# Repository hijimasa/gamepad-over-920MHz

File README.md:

# gamepad-over-920MHz

**USB ゲームパッドを 920MHz 帯（IM920sL）で無線化する**ファームウェアです。
Bluetooth より遠くまで届く無線リンクに載せ替えつつ、PC からは**普通のゲームパッドのまま**に見せます。
ロボットの遠隔操縦を想定しています。

```
[USBゲームパッド] ─USB(PIO-USB)→ [送信機 XIAO RP2040] ─UART→ [IM920sL]
                                                                 │ 920MHz
[PC] ←USB HID + CDC─ [受信機 XIAO RP2040] ←UART─ [IM920sL] ←─────┘
```

## 特徴

- **軸番号・ボタン番号が元のパッドと一致する。** 送信機がパッドの HID レポート
  ディスクリプタを解析して軸構成を無線で送り、受信機がそれに合わせて HID
  ディスクリプタを実行時に組み立てます。**受信機側の設定は不要**で、
  `/dev/input/js0` の番号が直挿しと同じになるので、既存のソフトをそのまま使えます。
- **フェイルセーフ。** 有効なパケットが 300ms 途絶えると、受信機は全軸中立・
  全ボタン OFF を出力します（実測で約 300ms、ログにも残ります）。
- **リンクの生死が送信機側でも分かる。** 受信機から 2 秒ごとにハートビートを返し、
  「受信機が前方向を受信できているか」まで含めて LED に反映します。
- **チャンネル自動選定。** 起動時に 31〜45 の雑音を測って空いているチャンネルへ移動します。
  複数ペアを同時に運用しても電波を取り合いません。通信が途絶えたら待ち合わせ用の
  ch31 へ自動で戻ります。
- **暗号化（AES-GCM 256bit）。** 同じグループ番号さえ合えば誰でも操作できてしまう
  状態を防げます。
- **USB CDC コンソール。** 設定・ペアリング・電波品質の確認・配線の切り分けができます。

Linux と Windows の両方で動作を確認しています（macOS は未確認ですが、標準の HID と
CDC しか使っていないため動く見込みです）。

## 必要なもの

| | 品目 | 備考 |
|---|---|---|
| 送信機 | Seeed XIAO RP2040 ×1 | CPU 240MHz で動かす（PIO-USB の要件） |
| 送信機 | IM920sL ＋ IM920sL-ADP ×1 | 変換アダプタ経由で 2.54mm に |
| 送信機 | USB Type-A メスコネクタ | ゲームパッド接続用 |
| 送信機 | モバイルバッテリー | 実測の消費電流は約 60mA |
| 受信機 | Seeed XIAO RP2040 ×1 | PC に USB-C で接続 |
| 受信機 | IM920sL ＋ IM920sL-ADP ×1 | |

配線は [docs/schematic/gamepad_wireless_schematic.svg](docs/schematic/gamepad_wireless_schematic.svg)（Rev.3）、
部品表は [docs/gamepad_wireless_BOM.xlsx](docs/gamepad_wireless_BOM.xlsx) を参照してください。

基板（送信機・受信機で共通、100×62mm 2層）の KiCad データと発注用ガーバーは
[hardware/](hardware/) にあります。ブレッドボードやユニバーサル基板で組む場合は
[docs/netlist.md](docs/netlist.md) にネットリストとレイアウト制約があります。

> IM920sL 本体と変換アダプタの取扱説明書は、メーカー（インタープラン）の配布物なので
> リポジトリには含めていません。<https://www.interplan.co.jp/> から入手し、
> `docs/IM920sL_manual.pdf` / `docs/IM920sL_ADP_manual.pdf` として置くと、
> 本 README 中の参照（コマンド仕様・端子表・チャンネル表）と対応します。

## 最短の始め方

```bash
# 1. ビルド環境（arduino-cli）
arduino-cli config add board_manager.additional_urls \
  https://github.com/earlephilhower/arduino-pico/releases/download/global/package_rp2040_index.json
arduino-cli core update-index
arduino-cli core install rp2040:rp2040
arduino-cli lib install "Pico PIO USB" "Adafruit NeoPixel"

# 2. 書込み
./build.sh rx upload /dev/ttyACM0   # 受信機
./build.sh tx upload /dev/ttyACM1   # 送信機

# 3. ペアリング（初回だけ。両機を 50cm 以内に置く）
#    起動後 5 秒以内（LED が水色の速い点滅）か、赤点滅中に
#    受信機 → 送信機 の順に BOOTSEL を 3 秒以上長押し

# 4. 確認
tools/jsinfo.py 10     # /dev/input/js0 の軸数・ボタン数とライブの値
```

うまくいくと**両機とも緑点灯**になり、PC に `irlab Wireless Gamepad` として
ゲームパッドが現れます。

詳しい操作は[操作（BOOTSEL ボタン ／ CDC コンソール）](#操作bootsel-ボタン--cdc-コンソール)、
うまくいかないときは[診断に使えるコマンド](#診断に使えるコマンド)を参照してください。

## 免責

**個人が趣味・研究用に作った原理試作です。**動作・性能・安全性のいずれも保証しません。

- 無線の到達距離や通信の安定性は、設置場所の電波環境に大きく左右されます。
  同じ構成でも結果は異なります。
- ロボットなど**物理的に動くものを制御する用途では、本装置とは独立した非常停止手段を
  必ず用意してください。**受信側に 300ms のフェイルセーフを実装してありますが、
  これは「通信が途絶えたら中立を出力する」だけのもので、機器の安全を保証するものでは
  ありません。
- 本リポジトリの成果物（ファームウェア、回路図、基板データ、資料）を使用した結果
  生じたいかなる損害についても、作者は責任を負いません。
- 920MHz 帯の利用は国と地域の法令に従ってください。IM920sL は日本国内の電波法認証を
  取得済みの製品ですが、**モジュールを改造したり国外で使用したりする場合は、
  使用者の責任において適法性を確認してください。**

不具合や改善点を見つけたら Issue や Pull Request で教えていただけると助かります。

## ライセンス

MIT License（[LICENSE](LICENSE)）。無保証です（上記「免責」および LICENSE の
"AS IS" 条項を参照）。

---

以下は実装と実機検証の詳細です。立ち上げで踏んだ問題（PIO-USB の 240MHz 要件、
TxD/RxD 逆接続の切り分け、コア1 だけが死ぬ故障モードなど）も記録してあります。

## ビルドと書込み

```bash
./build.sh tx                       # 送信機をビルド
./build.sh rx                       # 受信機をビルド
./build.sh tx upload /dev/ttyACM0   # ビルドして書込み
```

必要な環境:

- arduino-cli ＋ `rp2040:rp2040`（earlephilhower コア）
- ライブラリ `Pico PIO USB`、`Adafruit NeoPixel`
- FQBN
  - TX: `rp2040:rp2040:seeed_xiao_rp2040:usbstack=tinyusb,freq=240`
    （PIO-USB は 12MHz の倍数が必要。**120MHz ではタイミング余裕が足りず列挙に失敗した**ので 240MHz。
    `WG_FREQ=120 ./build.sh tx` で変更可）
  - RX: `rp2040:rp2040:seeed_xiao_rp2040:usbstack=tinyusb`

書込みは 1200bps タッチで自動的にブートローダへ入る。入らないときは BOOTSEL を押しながら
USB を挿し、`RPI-RP2` に `build/<role>/*.uf2` をコピーする。

## 構成

```
firmware/common/     TX・RX 共通（arduino-cli には --library で渡す）
  packet.h           無線パケット（State 12 バイト / Info 10 バイト）
  im920sl_config.h   IM920sL の設定・送受信（元からあったもの＋追記）
  im920_diag.h       配線切り分け用の diag / raw / scan
  hid_gamepad_map.h  パッドの HID ディスクリプタを解析して状態を取り出す（TX）
  hid_desc_builder.h HID ディスクリプタを実行時に組み立てる（RX）
  status_led.h       オンボード LED の状態表示
firmware/tx/tx.ino   送信機
firmware/rx/rx.ino   受信機
tools/console.py     CDC コンソールにコマンドを送る補助ツール
```

## 状態表示 LED

XIAO RP2040 のオンボード NeoPixel（GPIO12／電源 GPIO11）と三色 LED（R17/G16/B25）を同時に駆動する。

| 色 | 状態 |
|---|---|
| 赤の点滅 | 接続なし（TX: パッド未接続か送信が通らない／RX: フェイルセーフ中） |
| 黄の点滅 | ペアリング中 |
| 緑の点灯 | 接続中（送信機は**受信機からの応答が届いている**ときだけ） |
| 青の点灯 | 設定ブリッジ中 |
| 白の点滅 | 起動処理中 |
| **水色の速い点滅** | **BOOTSEL ボタン受付中（起動直後 5 秒）** |
| 赤紫の速い点滅 | IM920sL の設定に失敗 |

## 操作（BOOTSEL ボタン ／ CDC コンソール）

SW1 は未実装なので **BOOTSEL ボタン**を使う。電源投入時に押したままだと書込みモードに
入ってしまうため、**電源を入れてから押す**必要がある。押せるタイミングは 2 つ:

**1. 起動直後の受付ウィンドウ（LED が水色の速い点滅、5 秒間）**

電源を入れると 白点滅（起動処理）→ **水色の速い点滅（受付中）** と変わる。
水色の間に押す。

**2. 運用中、リンクが確立していないとき（LED が赤点滅）**

組み立て直後でまだペアリングしていない状態は赤点滅になるので、**そのまま押せばよい**。
緑点灯（正常動作中）のときはボタンを一切読まないので、運用中の通信を乱すことはない。

- 短押し（3 秒未満）→ 設定ブリッジ
- **3 秒以上の長押し → ペアリング**（TX＝子機、RX＝親機。両機を 50cm 以内に置く）

押している間は LED が黄点滅になるので、3 秒の長押しはそれを見ながら数えられる。

> BOOTSEL の読み取りは XIP（フラッシュ実行）を一瞬止めてもう一方のコアを idle にするため、
> PIO-USB が動作中は避けたい。そのため送信機では、パッドが列挙済みになるか起動から
> 15 秒経つまでは運用中のポーリングを行わない。

### 組み立て後の初回手順

1. 受信機を PC に、送信機にゲームパッドとモバイルバッテリーを繋ぐ
2. 両方とも赤点滅になる（＝まだペアリングしていない）
3. 両機を 50cm 以内に置く
4. **受信機の BOOTSEL を 3 秒以上長押し**（親機として登録パケットを送る）
5. すぐに**送信機の BOOTSEL も 3 秒以上長押し**（子機として受け取る）
6. 成功すると両方とも緑点灯になる

ペアリングは Flash に保存されるので**初回だけ**でよい（[ペアリングは初回だけ](#ペアリングは初回だけ) 参照）。

USB-C の CDC コンソール（`tools/console.py` か `screen /dev/ttyACM0 115200`）:

| コマンド | 内容 |
|---|---|
| `help` | コマンド一覧 |
| `status` | IM920sL の設定値、受信状況（RSSI・seq 欠番）、パッドの状態 |
| `config` | AutoConfig（目標値と違う項目だけ ENWR で書込み） |
| `pair` | ペアリング |
| `bridge` | USB CDC ↔ IM920sL の透過ブリッジ |
| `dump` | （TX）HID 生レポートの表示 |
| `map` | （TX）解析した HID マップ |
| `profile` / `reset` | （RX）HID 構成の表示／既定値に戻して再起動 |
| `diag` / `raw <cmd>` / `scan` | IM920sL の配線・応答の切り分け |

## ペアリングは初回だけ

グループ番号は `ENWR` でモジュールの Flash に書かれる不揮発設定なので、電源を切っても残る。
実測（両機を再起動して確認）:

```
再起動前: TX RDGN=0001D9D8 / RX RDGN=0001D9D8
再起動後: TX RDGN=0001D9D8 / RX RDGN=0001D9D8   ← 保持
link: UP  RSSI=-19dBm  packets=116 bad=0        ← 自動で復帰
```

ペアリングが要るのは **初回**と、**どちらかのモジュールを交換したとき**
（グループ番号は親機の固有 ID から決まる）、あるいは `RDGN` が `FFFFFFFF` に
戻ってしまったときだけ。**ファームを書き直しても不要**（`im920AutoConfig()` は
STNN/STRT/STCH/STPO/STTR しか触らない）。

⚠ Flash の書換えは全項目合計で 10 万回まで。ペアリングを不必要に繰り返さないこと。
`im920AutoConfig()` も「目標値と違う項目だけ」書くので、設定が合っていれば書き込まない。

## 軸番号・ボタン番号を元のパッドに合わせる仕組み

既存の操縦ソフトが `/dev/input/js0` を直接読んでいる場合、軸とボタンの並びが
元のパッドと一致していないと、受信機に差し替えた途端に割り当てがずれる。
joydev は **ABS\_\* コードの昇順**に軸番号を振る
（X=0, Y=1, Z=2, Rx=3, Ry=4, Rz=5, Hat=6,7）ので、**元のパッドに在る軸の集合**が
一致していれば番号も一致する。そのため、

1. TX は VID:PID の決め打ち表ではなく、**HID レポートディスクリプタを解析**して
   Usage（X, Y, Z, Rx, Ry, Rz, Hat switch, Button 1..n）の位置を求める。
   → どのパッドでも Linux の hid-generic と同じ割り当てになる。
2. TX は軸の種類（axisMask）とボタン数を **Info パケット**で 2 秒ごとに送る。
3. RX は受け取った構成を EEPROM に保存し、**HID ディスクリプタを実行時に組み立てる**。
   構成が変わったときは保存して自動で再起動し、新しいディスクリプタで列挙し直す。

つまり **受信機側の設定は不要**。送信機にパッドを繋げば、受信機が自動的に同じ形の
ゲームパッドとして PC に見えるようになる（初回は 1 回だけ自動再起動する）。

`dump` で生レポート、`map` で解析結果、RX の `profile` で現在の構成を確認できる。

## Linux 以外の OS で使えるか

受信機は標準的な **USB HID ゲームパッド＋CDC の複合デバイス**なので、Windows / macOS でも
追加ドライバなしで動く。実際のディスクリプタ:

```
bDeviceClass 239 / bDeviceSubClass 2 / bDeviceProtocol 1   ← IAD 複合デバイス宣言
  インタフェース 0,1: CDC（Communications + CDC Data）
  インタフェース 2  : HID（Usage Page = Generic Desktop, Usage = Game Pad）
```

- **HID**: Windows 標準の HID ドライバで動く。`joy.cpl`・DirectInput・RawInput から見える。macOS も標準対応
- **CDC**: Windows 10/11 は `usbser.inf` 内蔵で COM ポートとして見える。macOS は `/dev/cu.usbmodem*`
- **IAD 宣言**がないと Windows が複合デバイスを正しく分解できないが、TinyUSB が付けている

### 注意点

- **XInput ではない**。Windows で XInput 専用のゲームからは見えない。
  これは F310 を D モードで使うのと同じ制約。
  DirectInput / RawInput 対応のソフトなら問題ない。
- 軸・ボタン番号は、Linux の joydev が ABS コード順、Windows の DirectInput が
  HID Usage 順で決まるので、同じ Usage を出している限り一致するはず。**Windows 実機は未確認**。
- VID:PID は Adafruit の既定値 `239a:cafe` のまま。機能上は問題ないが、
  外部に配布するなら自前の PID を用意するのが望ましい。

### Windows 向けに入れてある対策

1. **シリアル番号の衝突回避** — 手元の 2 枚は同じチップ ID（`4250305539333104`）を返す。
   Windows は VID/PID/シリアルでインスタンスを識別するため、同じ PC に両方挿すと衝突しうる。
   役割の接頭辞を付けている（`WGTX-...` / `WGRX-...`）。
2. **HID ディスクリプタのキャッシュ対策** — Windows はレポートディスクリプタを
   VID/PID/**REV** 単位でキャッシュする。受信機はプロファイル学習でディスクリプタを
   作り直すので、構成から `bcdDevice` を生成して別リビジョンとして見せている
   （例: axisMask 0x27・ボタン 12・ハットあり → `bcdDevice = 27.19`）。

## 取扱説明書との照合（docs/IM920sL_manual.pdf Rev.1.5）

公式資料と全コマンド・全設定値を突き合わせ済み。**仕様違反は無かった。**

- **ch31＋高速モード（STRT 1）は仕様上有効**。`STCH` は「01〜29、31〜45」とだけ規定され、
  通信モードによる制限は無い（モードが決めるのは既定値のみ）。
  4s モード（31〜45）は「1 時間あたりの送信時間の総和 **制限なし**」と明記。
  電波法上の処理はモジュール内部で自動なので、ファーム側で duty を管理する義務は無い。
- 発行している 14 コマンドの名称・引数書式・応答・前提条件・順序依存はすべて資料どおり
  （`STNN 0001` に ENWR 必須、`STRT`→`STCH` の順、ペアリング後は RESET 端子必須）。
- 受信行 `aa,bbbb,dd:`、**RSSI は符号付き**（`9Ch`=−100dBm）、TXDA は 1〜32 バイト、
  送信時間 `4.56ms + 80µs × バイト数`（12 バイトで 5.52ms）— すべて一致。
- 触っている設定は次の 5 つだけ（それ以外は初期値のまま）。

  | コマンド | 内容 | 設定値 |
  |---|---|---|
  | `STNN` | ノード番号 | 受信機（親機）= **0001**、送信機 = **0002** |
  | `STRT` | 通信モード | **1**（高速 100kbps） |
  | `STCH` | チャネル | **31**（起動後に空きチャネルへ移動） |
  | `STPO` | 送信出力 | **2**（10mW） |
  | `STTR` | キャリアセンス NG 時の自動リトライ | **00**（再送はファーム側で判断する） |

- **ADP の J1/J2 対応**も回路図で確認。`J1-n = 本体 pin(2n−1)`、`J2-n = pin(2n)`。
  本体 pin1 は資料により `IO1/BUSY`、ADP 回路図では `IO1/RTS` と表記が違うが同じ端子。

### ユニキャストと ACK について

`TXDU`（ユニキャスト）は実在し「**OK は相手に届いたことを示す**」と明記されている。
ただし**ルート探索を行い、失敗時は自動で最大 10 回リトライ**するため遅延が大きくばらつく
（資料も「リアルタイム性が要求される用途では十分ご注意ください」と注意喚起）。
30ms 周期の操縦データには不向きなので採用していない。

各パケットは差分ではなく**現在の全状態**を持つので、落ちても次のパケットが完全に
上書きする。再送は「古い状態を届けたうえに新しい状態を遅らせる」ため逆効果。
取りこぼしへの対処は受信側の 300ms フェイルセーフで行う。

なお `TXSB`（センドバック送信）はルート探索なしで送信元へ返せるので、
ハートビートをブロードキャストからユニキャストに変えたい場合の選択肢になる（未採用）。

### 4s モードの送信休止規定（2026-09-19 に再確認）

取扱説明書 表1・§7-3 より、ch31〜45（4s モード）の規定は次のとおり。

| 項目 | 4s モード（ch31〜45） | 360s モード（ch01〜29） |
|---|---|---|
| キャリアセンス時間 | 約 6ms | 128µs〜1ms |
| 送信休止時間 | **52ms 以上** | 2ms 以上 |
| 1 時間あたりの送信時間の総和 | **なし** | 360 秒以内 |
| 送信時間制限 | 3.9 秒以下 | 400ms 以下 |

「1 時間 360 秒」の総和制限は ch01〜29 だけの話で、本プロジェクトの ch31〜45 には無い。

代わりに効くのが**送信休止 52ms** で、挙動は「最初の送信から 3.9 秒を超えたら 52ms 休止」
「4 秒経過前に 52ms 以上空けば窓がリセットされる」。
1 回の占有はキャリアセンス約 6ms ＋ 送信 6ms（12 バイト時 5.52ms を切り上げ）＝ 約 12ms
なので、計算上は **64ms 間隔**あれば窓がリセットされ続けるはず。

**ただし実測はこの計算と合わない。** ブリッジ経由でファームを介さず TXDA を打った結果:

| 送信間隔 | 55ms | 65ms | 75ms | 90ms | 120ms | 150ms |
|---|---|---|---|---|---|---|
| NG 率 | 20.0% | 17.5% | 12.5% | 8.0% | 4.0% | **0%** |

64ms を超えても NG は残り、0 になるのは 150ms 以上。**機構は特定できていない。**

なお **NG は一度も連続しなかった**（90ms で 12 回、120ms で 6 回、すべて単発）。
欠落は最悪 2 周期分なので、受信側フェイルセーフ 300ms には届かない。

⚠ 暗号化を有効にすると 1 パケットが **24 バイト増える**（§7-4）ので、
12 バイトのパケットは 36 バイト相当（7.44ms）になる。上の測定は暗号化なしの値。

## UART の高速化（115200bps）

12 バイト送信の UART 時間は 19200bps で約 16ms あり、**電波の送信時間 5.5ms の 3 倍**を
食っていた。`SBRT 7` で 115200bps にすると約 2.7ms になる。

`SBRT` は資料に「Flash メモリに記憶します」の記載が無く揮発性とみられるため、
**毎起動で設定しても Flash 書換え回数を消費しない**。起動時に `im920SetupBaud()` が
`RDVR` の応答でモジュールの現在のボーレートを判別し、必要なら 115200 に上げる。
判別に失敗したときは元のボーレートのまま動作を続ける。

## パケット暗号化＋送信元認証

AES-GCM 256bit。**同じグループ番号さえ合えば誰でもロボットを操作できる**状態を防ぐ。

```
enc <16進64桁>   キーを設定して有効化（両機に同じキーを入れること）
enc off          無効化（キーは残る）
```

- `STKY` は ENWR 中のみ実行可能で Flash に記憶される（読出しコマンドは無い）ため、
  明示的なコマンドのときだけ設定する
- 通信時間が 24 バイト分（高速モードで約 1.9ms）増える
- ペアリング（STGN）時は常に非暗号化パケットなので、順序はどちらでもよい
- 実測: 暗号化オンで `ng=0%`、`bad=0`、`lostEvents=0`

## 無線パケット

**State（12 バイト。30〜100ms ごと）**

| オフセット | 内容 |
|---|---|
| 0 | seq |
| 1–2 | buttons（u16 LE、bit0 = ボタン 1） |
| 3 | hat（0〜7 が方向（0=上、時計回り）、8 = 中立） |
| 4–9 | 軸 6 個 = **X, Y, Z, Rx, Ry, Rz**（0x80 が中立。スティック/トリガではなく **HID Usage 順**で並べている。理由は「軸番号・ボタン番号を元のパッドに合わせる仕組み」を参照） |
| 10 | flags（bit0: パッド接続中） |
| 11 | checksum（byte0〜10 の XOR） |

**Heartbeat（4 バイト。受信機 → 送信機、2 秒ごと）**
`0xC3`, seq, 受信機側の RSSI(i8), XOR。

`TXDA` はブロードキャストで ACK がないため、送信機は自分の電波が届いたかを知る手段がない。
そのままだと送信機の緑は「モジュールが送信を受理した」ことしか意味せず、
**受信機の電源が落ちていても緑**になってしまう。そこで受信機から定期的に投げ返し、
送信機はこれが 1.5 秒途切れたら赤点滅にする。受信機側の RSSI も載せているので、
送信機のコンソールで**両方向の電波強度**が見える（距離試験に便利）。

⚠ **周期を短くすると前方向のパケットが落ちる。** 半二重なので、受信機が
ハートビートを送っている間はパッドのパケットを受け取れない。実測:

| ハートビート周期 | 受信パケット | seqDrop | 300ms 途絶の回数 |
|---|---|---|---|
| 500ms | 11502 | 901（7.8%） | 870 |
| 2000ms | 203 | 0（0%） | 0 |

送信機の NG 率（キャリアセンス）は 2Hz でも +1% 程度しか増えないので、
一見すると安く見えるが、**効いてくるのは受信側の取りこぼし**のほう。
既定は 2 秒、送信機のリンク判定タイムアウトは 5 秒。
受信機は応答を待たずに投げる（`im920SendNoWait`）ので HID の処理は止まらない。

**Info（10 バイト。2 秒ごと）** `0xA5`, version, axisMask, buttonCount, caps(bit0=hat), VID, PID, XOR。
長さでどちらのパケットか判別する。

送信は「状態が変わったら即送信＋無変化でも 100ms ごと」「最短間隔 30ms」。`TXDA` が NG でも
再送はせず次の周期に任せる。

## 動作中に突然リンク断になる問題（2026-09-19 修正）

送信機のモジュールは**半二重**で、自分が送信している間は受信できない。
そのため送信間隔によって、受信機からのハートビートの取りこぼし率が大きく変わる。

| 送信間隔 | ハートビート欠落 |
|---|---|
| 60ms（パッド静止） | 6.6% |
| **30ms（操作中）** | **29.5%** |

ハートビートは 2 秒周期なので、旧設定の `HB_TIMEOUT_MS = 5000` では
**2 回連続で落ちるだけ**（操作中は 8.7%／2 秒ごと）でリンク断と誤判定していた。
平均 20〜30 秒に 1 回、動作中に突然赤点滅する原因。

さらに `CH_REVERT_MS = 12000` も同じハートビート頼りで、6 回連続の欠落で
ch31 に戻って再走査に入る。受信機が取り残されるので**本当の通信断**になっていた。

| 定数 | 変更前 | 変更後 | 必要な連続欠落 |
|---|---|---|---|
| `HB_TIMEOUT_MS` | 5000 | **15000** | 2 回 → 7 回 |
| `CH_REVERT_MS` | 12000 | **30000** | 6 回 → 15 回 |

ロボットの保護は受信側の 300ms フェイルセーフが行うので、送信側のリンク判定を
鈍くしても安全性は落ちない（送信機の LED は状態表示にすぎない）。

修正後、操作中相当（30ms 連続送信）で 225 秒間、`link: DOWN`・再走査とも 0 回。
またハートビートの欠落自体も 29.5% → 約 7% に下がった。誤判定による再走査が
さらにハートビートを失わせる悪循環になっていたとみられる。

**半二重による取りこぼし自体は解消していない。** しきい値を実測に合わせた修正である。

## `pad: reports` が増えないのは異常ではない

送信機の `status` が出す `reports` は、**パッドから HID レポートが届いた回数**。
多くのゲームパッド（Logitech F310 など）は状態が変化したときだけレポートを返すので、
**パッドを触っていなければ `reports=1` のまま**になる。これは正常。

実際に操作すると増える（実測で 2512 まで上がることを確認済み）。
PIO-USB が死んでいるかどうかは `usb` コマンドの
`epErr` / `epStall` / `コア1: loop1 通算` で判断すること。

## 動作中の突然の再起動＝core1（PIO-USB）の停止

送信機に**再起動しても消えないブラックボックス記録**（`__uninitialized_ram`）を入れて
現行犯で捕らえた結果、原因が確定した。

```
ブラックボックス: ソフト再起動 1 回 / 赤点滅 1 回
  赤点滅の内訳: パッド切断=1 USBホスト停止=0 ハートビート途絶=0 受信機側=0
  直近の自動再起動: コア1(PIO-USB)の停止
                    （稼働 265717ms, reports=1 ok=2764 ng=309, ハートビート 223ms 前）
```

- **無線は無関係。** 停止時点でハートビートは 223ms 前に届いており、リンクは健全だった
- 赤点滅の原因は**パッド切断**で、その 9 秒後に監視機構が再起動をかけている
- `loop1()` は `g_hostTicks++` が先頭なので、止まっているのは **`USBHost.task()` の中**

受信機側のログで実際の通信断も測れた:

```
途絶 6 回 / 継続時間: [0, 1, 10, 14, 2988, 20930] ms
```

**20.9 秒**の内訳は「core1 停止の検出待ち 10 秒 ＋ 再起動 ＋ チャンネル再走査」。
再起動後は ch31 から始まるため、受信機が待ち合わせに戻るまで待つことになっていた。

### 対策（根本原因ではなく復帰時間）

`USBHost.task()` が固まる原因はライブラリ内部で手が出ないため、**復帰を速くする**方針。

| 項目 | 変更前 | 変更後 |
|---|---|---|
| `HOST_REBOOT_MS`（停止と判断するまで） | 10000 | **3000** |
| 再起動後のチャンネル | ch31 から再会合 | **停止直前の ch へ直接復帰**（再走査なし） |

core1 は常時回っているので 3 秒止まれば確実に死んでいる。
またチャンネルをブラックボックスに保存しておけば、受信機はそこに残っているので
再会合が不要になる。合わせて通信断は 21 秒 → 数秒に縮む見込み。

**根本原因（`USBHost.task()` が固まる理由）は未解明のまま。**

### ネイティブ USB ホストへの移行を検討し、断念した（2026-09-19）

PIO-USB をやめて RP2040 の**ネイティブ USB コントローラ**をホストにすれば、
core1 も PIO も USB に関与しなくなり、この停止は構造的に消える。
XIAO の USB-C に OTG 変換でパッドを繋ぎ、給電は J1 から入れる構成。

- arduino-pico は `usbstack=tinyusb_host`（Adafruit TinyUSB Host (native)）に対応
- 5V ピンから USB-C の VBUS へ逆流することは実機で確認済み（J1 給電で動作した）

最小構成（[firmware/hosttest/](firmware/hosttest/)）で検証した結果:

| 段階 | 結果 |
|---|---|
| `USBHost.begin(0)` | ✅ 通る |
| USB 機器の検出（`tuh_mount_cb`） | ✅ 呼ばれる |
| HID として列挙（`tuh_hid_mount_cb`） | ✅ 呼ばれる。VID:PID も取得できる |
| `tuh_hid_receive_report()` | ✅ 成功を返す |
| **レポートの受信** | ❌ **一度も届かない** |

`rearm=0 rep=0` が延々と続く（`rearm=0` は「転送が保留中」を意味し正常）。
つまり**転送は armed のまま完了しない**。ゲームパッドでもマウスでも同じ。
同じ TinyUSB の HID クラスドライバで PIO-USB 版では動くので、
差分はネイティブ HCD の割り込み IN 転送にある。

`hcd_rp2040.c` を読んだ限り実装は構造的に正しく見え（割り込みエンドポイントは
15 個のプールから確保、`bInterval` 設定済み、SOF も有効化）、
設定漏れのような分かりやすい原因は見当たらなかった。

**これ以上はライブラリ内部のデバッグになるため打ち切った。**
検証用スケッチは最小再現コードとして残してある。

### NeoPixel との干渉を疑って調べたこと

`Adafruit_NeoPixel::show()` は RP2040 で PIO を使う経路でも、実行中ずっと
`noInterrupts()` で割り込みを止める（Adafruit_NeoPixel.cpp:459 と :3336）。
ただし arduino-pico の `noInterrupts()` は `get_core_num()` でコア別に管理されており
（wiring_private.cpp:81）、**core0 で止めても core1 の割り込みは止まらない**。
`show()` は core0、PIO-USB は core1 なので、割り込み阻害が直接の原因という線は薄い。

とはいえ NeoPixel と PIO-USB は **PIO ハードウェアを共有**しており
（そのため `enableNeoPixel()` は `USBHost.begin()` の後に呼ぶ必要がある）、
静的解析だけでは否定しきれない。切り分けのため `neo on|off` コマンドを用意した。
`off` にすると NeoPixel の PIO を確保せず、三色 LED（R=17/G=16/B=25）だけで
状態表示する。設定は EEPROM に保存され、再起動しても残る。

**まだ結論は出ていない。** core1 停止は数分〜数十分に 1 回の頻度なので、
`neo off` で長時間動かして `ブラックボックス` の再起動回数を比較する必要がある。

## 未解明：送信後に消える約 15% のパケット

`TXDA` が OK を返したのに受信機に届かないパケットが約 15% ある。
**実害は確認できていない**が、原因も特定できていないので記録しておく。

切り分けで否定できたもの:

| 疑い | 検証方法 | 結果 |
|---|---|---|
| 電波干渉 | ch31〜45 の RSSI を実測 | −105〜−110dBm。キャリアセンス閾値 −80dBm 超過は 0 |
| 受信機の取りこぼし | `Serial1.overflow()`、行の解析結果を計測 | FIFO 溢れ 0、解釈不能 0、他ノード 0 |
| 受信機の処理落ち | `loop()` の最大間隔を計測 | 最大 22ms（FIFO 溢れの閾値未満） |
| パケット破損 | チェックサム失敗を計測 | `bad=0` |
| ハートビートとの衝突 | `hb off` で比較 | 18.7% / 21.1%。ほぼ差なし |
| 至近距離による受信機の飽和 | 送信出力 10mW / 1mW で比較 | RSSI −12dBm で 21.1%、−21dBm で 22.9%。変わらず |
| 送信間隔 | 60ms / 90ms で比較 | 14.6% / 19.8%。改善せず |

**欠落は必ず単発**（1 個が大半、2 個が数回、3 個以上は 0）。
最悪の空きは約 90〜180ms で、受信側フェイルセーフ 300ms には届かない。
実効更新レートが 2 割ほど落ちるだけで、操作が途切れる現象には繋がっていない。

モジュール内部で CRC を通らなかったパケットが黙って捨てられている可能性が高いが、
モジュールから受信エラー数を読む手段が無いため確認できていない。

## フェイルセーフ

- 有効なパケットが **300ms** 届かない、または flags.bit0 = 0 のとき、RX は全ボタン OFF・
  軸中立・ハット中立の HID レポートを出す。
- 途絶の開始と復帰を CDC にログ出力し、LED を赤点滅にする。
- TX 側もパッドが外れたら中立＋flags.bit0 = 0 を送る。

## 実機の状況（2026-09-18 時点）— **通しで動作**

送信機・受信機とも動作し、パッド → 920MHz → PC の経路が通った。

```
送信機 TX: pad connected  VID:PID=046D:C216 axisMask=0x27 buttons=12 hat=1
           tx: ok=143 ng=0 (0%)   送信間隔 30ms
受信機 RX: link UP  RSSI=-12〜-33dBm  packets=1334 bad=0
           profile: axisMask=0x27 (X Y Z Rz) buttons=12 hat=1  src=046D:C216
PC:        /dev/input/js0 "irlab Wireless Gamepad"  軸 6 個 / ボタン 12 個
```

軸・ボタンの数が元の F310（D モード）と一致している。受信機は送信機から届いた
Info パケットでパッド構成を自動学習し、EEPROM に保存して HID ディスクリプタを
作り直した（ログ: `パッド構成が変わりました: axisMask 0x3F->0x27 buttons 16->12`）。

### 立ち上げでつまずいた点（記録）

**1. IM920sL が無応答 → TxD/RxD の逆接続（両基板とも）**

`swap` コマンド（ソフト UART で GPIO1 送信／GPIO0 受信）で確定した:

```
TxD/RxD 逆接続テスト（GPIO1 から送信し、GPIO0 で受信する）
  リセット後の受信: 19 バイト  "IM920sL Ver.01.12"
  RDVR の応答:      19 バイト  "IM920sL Ver.01.12"
```

D6/D7 を入れ替えて解決。1 枚目はさらに芋半田の手直しも必要だった。
判別の決め手は **BUSY ピン**で、生きているモジュールは BUSY を L に駆動し、
リセットで変化する（死んでいる側は H に固着したままだった）。

**2. USB ゲームパッドが列挙されない → CPU クロックと XInput**

- PIO-USB はビットバンギングのため **120MHz ではタイミング余裕が足りなかった**。
  アドレス 0 での通信と SET_ADDRESS までは成功し、アドレス 1 の転送が全滅する、
  という症状。**240MHz にして解決**（build.sh の既定値）。
- 繋いでいた F310 が **XInput モード**（046D:C21D, class 255/subclass 0x5D）で、
  HID ではないため HID ドライバが掴めなかった。背面スイッチを **D** にして解決。

**3. Adafruit_NeoPixel が PIO を使う**

RP2040 版の NeoPixel は `pio_claim_free_sm_and_add_program` で PIO を掴む。
PIO-USB は TX プログラムを PIO0 のオフセット 0 に置く必要があるため、
送信機では起動直後は三色 LED だけで表示し、`USBHost.begin()` の後に
`enableNeoPixel()` を呼ぶ順序にしてある。

### 確認できた設計上の疑問

- **高速モード（STRT 1）＋ ch31 は受け付けられた**（`RDCH=31` が読める）。
  時間総和の制限がない 4s モードが使えるので、送信頻度を落とす必要はない。
- ペアリング（STGN → RESET 端子で再起動）は成功し、親機・子機の `RDGN` が
  `0001D9D8` で一致した。子機は `GRNOREGD` を出力した。
- NG 率（干渉のない状態、`rate N` / `hb N` コマンドで測定）:

  | 条件 | NG 率 |
  |---|---|
  | 送信間隔 30ms・ハートビートなし | 1% |
  | 送信間隔 30ms・ハートビート 2Hz（既定） | 2% |
  | 送信間隔 30ms・ハートビート 4Hz | 3% |
  | 送信間隔 20ms（50Hz） | 1% |

  内訳はすべて「モジュールが NG」＝キャリアセンス失敗で、BUSY 待ちや無応答は 0。

### 外部干渉とチャンネル自動選定

測定中、ch31 の NG 率が一時的に 26〜41% まで悪化した。**送信間隔を 30→60→100ms と
広げても NG 率が変わらなかった**（26%→30%→34%）ことから、自分の送信が原因ではなく
外部の電波でチャンネルが塞がれていると判断できる。干渉は時間とともに移動し、
別の時点では ch35 が 63% に悪化した。**固定のチャンネル割り当てでは追随できない。**

そこで **ch31 を待ち合わせ専用**にして、送信機が起動時に空きチャンネルを選ぶ方式にした。

```
1. 起動時は両機とも ch31（AutoConfig が Flash の既定値に戻すので必ずここに来る）
2. ch31 でリンク確立（送信機は受信機のハートビートを待つ）
3. 送信機が 31〜45 を STCH で切り替えながら RDRS で雑音を測り、最も静かな ch を選ぶ
4. チャンネル変更通知（3 バイト）を 6 回送ってから、自分も移動
5. 受信機は通知を受けて移動
6. 双方とも「12 秒間 相手から受信が無ければ ch31 へ戻る」（片方だけ移動した場合の復帰）
```

**Flash を消費しない**のが利点。`STCH` は取扱説明書に「ENWR コマンド実行時は Flash
メモリに記憶します」の記載が無く揮発的なので、ENWR なしで発行すれば書換え回数
（全項目合計 10 万回）を使わない。EEPROM も使わない（送信機では `EEPROM.commit()` が
`rp2040.idleOtherCore()` を使うため、PIO-USB 稼働中の書込みはデッドロックの危険がある）。

実測:

```
起動 → 走査 → ch42 を選択・移動   tx ng=8%, bad=0, lostEvents=0

［復帰試験］受信機だけ ch38 に強制
  → リンク断（受信機は中立を出力）
  → 約12秒で両機とも ch31 へ復帰
  → 送信機が再走査して ch40 を選択・通知 → 両機 ch40 で確立、以降安定
```

### 複数ペアを同時に運用するとき

グループ番号で**論理的には分離される**（取扱説明書「グループ番号が一致するモジュールのみ
通信」）ので、他のペアのデータが混ざることはない。ただし同じチャンネルでは**電波を取り合う**
（キャリアセンスは「その通信チャンネルの RSSI 値が **-80dBm 以上**のときは NG」）。
手元で -21dBm なので、同じ部屋の別ペアは確実にこの閾値を超える。

上記の自動選定により、ペアごとに別チャンネルへ分かれる。

⚠ 複数ペアが同時に起動すると一時的に全機が ch31 に集まる。走査と移動は数秒で終わるが、
起動タイミングをずらせるならずらしたほうが確実。

`ch N`（31〜45）で手動指定もできる。送信機で実行すると受信機にも通知が飛ぶ。
どちらも揮発的なので、再起動すると ch31 に戻って改めて走査する。

`ttr N` でキャリアセンス NG 時の自動リトライ回数も変えられる（既定 00＝リトライなし）。
遅延と引き換えに NG を減らせるので、干渉が避けられない環境では選択肢になる。

### 診断に使えるコマンド

```bash
tools/console.py -p /dev/ttyACM0 -m 12 diag   # IM920sL の配線切り分け
tools/console.py -p /dev/ttyACM0 -m 12 swap   # TxD/RxD 逆接続の判定（決め手）
tools/console.py -p /dev/ttyACM0 -m 20 rscan  # リセットしながらボーレート総当たり
tools/console.py -p /dev/ttyACM0 -m 5 usb     # USB ホストの状態・線の静電容量
tools/console.py -p /dev/ttyACM0 "rate 20"    # 送信間隔を変えて NG 率を測る
tools/console.py -p /dev/ttyACM0 "ch 35"     # チャネル変更（測定用。再起動で戻る）
tools/console.py -p /dev/ttyACM0 "ttr 03"    # キャリアセンス NG 時のリトライ回数
tools/console.py -p /dev/ttyACM1 "hb 1000"   # ハートビート周期（off で停止）
tools/console.py -p /dev/ttyACM0 "enc <16進64桁>"  # 暗号化キー設定（両機に同じキー）
tools/jsinfo.py 10                            # js0 の軸数・ボタン数とライブの値
```

TinyUSB 本体のログを取りたいときは README 末尾の `wg_dbg.h` の項を参照。

## 残っている実機確認

1. [x] IM920sL が応答する
2. [x] `STRT 1` の後の `STCH 31` が OK になる
3. [x] ペアリングと `RDGN` の一致
4. [x] PIO-USB で元パッドが列挙され、`map` で解析できる
5. [x] 送信頻度ごとの NG 率。**初期の「30ms で 0%」は短時間の測定で、
       長時間動かすと 30ms で約 22%、60ms で約 8% になる**（2026-09-19 再測定）。
       NG は必ず単発で、次の周期で回復するため実害は無い。遅延の実測はこれから
6. [ ] `/dev/input/js0` として認識され、元のパッド向けに書かれたソフトが
       そのまま動くか（js0 としての認識と軸/ボタン数の一致までは確認済み。
       実アプリでの動作確認が残り）
7. [ ] フェイルセーフ（TX 電源断・アンテナ遮蔽）
8. [ ] モバイルバッテリーが低電流で自動 OFF しないか

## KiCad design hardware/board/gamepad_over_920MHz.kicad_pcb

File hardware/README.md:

# 基板データ（KiCad）

原理試作用の基板。送信機と受信機は **1 種類の基板**でまかなう
（受信機は USB-A まわりを実装しないだけ。[../docs/netlist.md](../docs/netlist.md) 参照）。

## 構成

```
hardware/
├── make_footprints.py   モジュール用フットプリントの生成
├── make_board.py        基板（配置・配線・ベタ・DRC・作図）の生成
├── make_checksheet.py   寸法確認用 1:1 印刷シートの生成
├── footprints.pretty/   生成されたフットプリント
├── board/               基板データ（.kicad_pcb）と確認用 PDF、DRC レポート
└── check/               確認シート（PDF/SVG）
```

フットプリントは手書きではなくスクリプトで生成している。寸法が判明したら
`make_footprints.py` の定数を直して再生成する。

## ⚠ 実装前に寸法を確認すること

**`check/footprint_check.pdf` を 100%（拡大縮小なし）で印刷し、実物を重ねて確認する。**
シートに 50.0mm の基準線を入れてあるので、まずそれを定規で測って印刷倍率を確かめる。

| 部品 | 寸法 | 根拠 |
|---|---|---|
| IM920sL-ADP | J1–J2 間 **25.4mm**、ピン1 は上端から 5.71mm、ピッチ 2.54mm×10、外形 30.0×40.0mm | 製品資料 Rev.1.0 外形寸法図で確認済み |
| XIAO RP2040 | 2 列の間隔 **15.24mm**（0.6in）、ピッチ 2.54mm×7 | 実測で確認済み |

どちらも実測で確定済みだが、発注前にもう一度確認シートを重ねること。
ここを間違えると基板が使えない。

## 生成と確認

```bash
python3 hardware/make_footprints.py     # フットプリント
python3 hardware/make_board.py          # 基板 + DRC + 確認用 PDF
python3 hardware/make_checksheet.py     # 確認シート
python3 hardware/make_gerber.py         # 発注用ガーバー + ドリル
```

`make_board.py` は実行のたびに `board/` を作り直し、最後に DRC を回して
`board/drc.txt` に結果を書く。**現状 0 violations / 0 unconnected pads。**

KiCad 6 の Python API（`pcbnew`）を使っている。KiCad 7 以降なら `kicad-cli` で
同じことがもっと簡単にできる。

## 基板の概要

| 項目 | 値 |
|---|---|
| 外形 | 100 × 62 mm、2 層 |
| 固定穴 | φ3.2（M3）× 4、四隅（4,4）（96,4）（4,58）（96,58） |
| 配線幅 | 0.4mm（全ネット） |
| クリアランス | 0.2mm（ベタは 0.3mm） |
| ベタ | 両面 GND。左上 22 × 20mm はアンテナ用に銅を抜いてある（シルクに `ANT KEEPOUT`） |

確認用の作図:

| ファイル | 内容 |
|---|---|
| `board/gamepad_over_920MHz-top.pdf` | 表面（F.Cu + シルク） |
| `board/gamepad_over_920MHz-bottom.pdf` | 裏面（B.Cu） |
| `board/gamepad_over_920MHz-layout.pdf` | 両面重ね |
| `board/placement.pdf` | 部品配置のみ |

## 発注データ

`make_gerber.py` が `board/gerber/` に一式を書き出し、
`board/gamepad_over_920MHz-gerber.zip` にまとめる。**この ZIP をそのまま業者に投げる。**

| 拡張子 | 内容 |
|---|---|
| `.gtl` / `.gbl` | 表面 / 裏面 銅箔 |
| `.gto` / `.gbo` | 表面 / 裏面 シルク |
| `.gts` / `.gbs` | 表面 / 裏面 レジスト |
| `.gtp` / `.gbp` | 表面 / 裏面 メタルマスク（手はんだなので未使用） |
| `.gm1` | 外形（100 × 62mm） |
| `-PTH.drl` | スルーホール 50 個（φ0.7 / 0.8 / 0.92 / 1.0 / 2.3） |
| `-NPTH.drl` | 固定穴 φ3.2 × 4 |

発注時の指定:

| 項目 | 値 |
|---|---|
| 層数 | 2 |
| 基板サイズ | 100 × 62 mm |
| 板厚 | 1.6mm |
| 銅箔厚 | 1oz |
| 表面処理 | HASL（有鉛・無鉛どちらでも可） |
| 最小線幅 / クリアランス | 0.4mm / 0.2mm（どの業者の標準仕様でも通る） |

**発注前に業者サイトのガーバービューアで必ずプレビューを確認すること。**
手元にビューアがないため、出力データの目視確認はできていない。

配置は次の条件で決めてある:

- **U2（IM920sL-ADP）は回転 0。** アンテナが J1 のピン1 付近から出るので、
  それが基板左上の空き側（ANT KEEPOUT）に来る。ADP は裏面にコネクタがあるため、
  **ピンソケットで嵩上げして実装する**
- **U1（XIAO RP2040）は 180 度回転。** USB-C が基板下端を向き、
  モバイルバッテリーのケーブルを基板外へ逃がせる
- **J1（USB-A）は変換基板を使わず直付け。** 右端に開口を向ける。
  シェル固定パッドは GND に落としてある

### D+/D− を表裏に分けている理由

XIAO 側は D0(D+) が D1(D−) の**下**、J1 側は D+ が D− の**上**で順序が逆転しており、
1 層では必ず交差する。そのため **D+ は表面、D− は裏面**に分けた。
フルスピード（12Mbps）で配線長 20mm 程度なので実用上は問題ないが、
インピーダンス整合は取っていない。

## 設計方針

レイアウトの制約は [../docs/netlist.md](../docs/netlist.md) にまとめてある。要点だけ再掲:

1. **IM920sL のワイヤーアンテナ周辺はベタ GND・配線・金属を置かない。** 基板端に寄せ、
   できればアンテナを基板外へ出す。飛距離に直結する
2. **USB の D+/D− は短く・等長。** R1/R2（22Ω）は XIAO 側に寄せる。
   PIO-USB はタイミング余裕が少ない（CPU 120MHz では列挙に失敗する）。
   ※ 実際の配線では並走ではなく表裏に分けている（理由は上記）
3. C3（0.1µF）は IM920sL の VCC 直近、C2（10µF）はその外側
4. C1（47µF）は USB-A の VBUS 直近

RF 性能は保証できない。原理試作として作り、実測しながら直す前提。

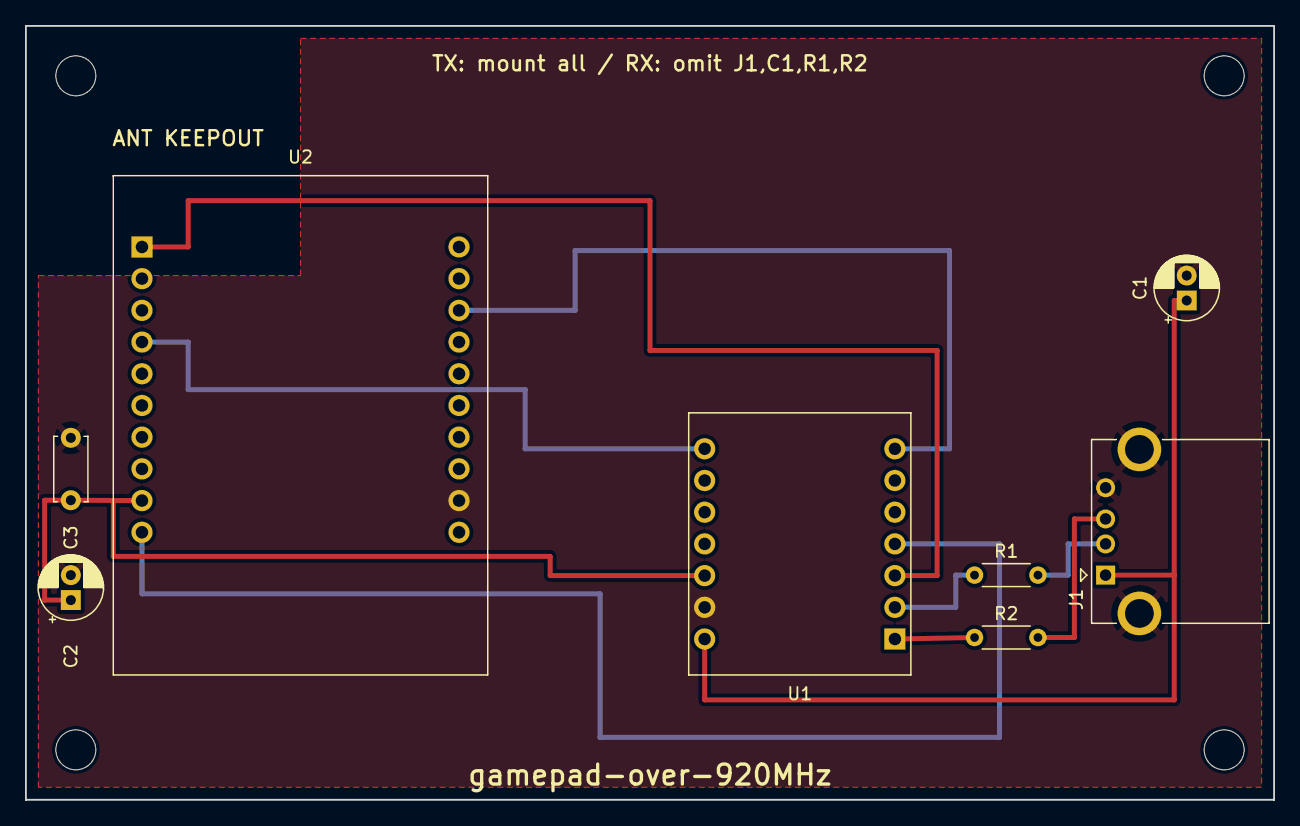
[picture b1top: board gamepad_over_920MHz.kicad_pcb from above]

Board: 2 copper layers, 100.0 x 62.0 mm, 12 parts (0 on the bottom side), 11 nets.

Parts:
C1, C2: CP_Radial_D5.0mm_P2.00mm
C3: C_Disc_D5.0mm_W2.5mm_P5.00mm
H1, H2, H3, H4: MountingHole_3.2mm_M3
J1: USB_A_CONNFLY_DS1095-WNR0
R1, R2: R_Axial_DIN0204_L3.6mm_D1.6mm_P5.08mm_Horizontal
U1: XIAO_RP2040
U2: IM920sL_ADP

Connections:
+3V3: C2.1, C3.1, U1.10, U2.9
+5V: C1.1, J1.1, U1.8
GND: C1.2, C2.2, C3.2, J1.4, J1.5, U1.9, U2.19
IM_BUSY: U1.3, U2.1
IM_RESET: U1.4, U2.10
IM_RXD: U1.7, U2.13
IM_TXD: U1.14, U2.4
USB_DM: R1.1, U1.2
USB_DM_CON: J1.2, R1.2
USB_DP: R2.1, U1.1
USB_DP_CON: J1.3, R2.2
